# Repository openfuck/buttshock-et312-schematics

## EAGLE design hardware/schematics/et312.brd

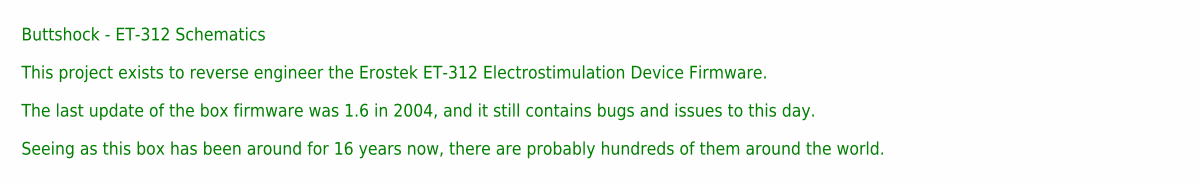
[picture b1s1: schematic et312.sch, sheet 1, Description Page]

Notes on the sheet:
Buttshock - ET-312 Schematics This project exists to reverse engineer the Erostek ET-312 Electrostimulation Device Firmware. The last update of the box firmware was 1.6 in 2004, and it still contains bugs and issues to this day. Seeing as this box has been around for 16 years now, there are probabl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

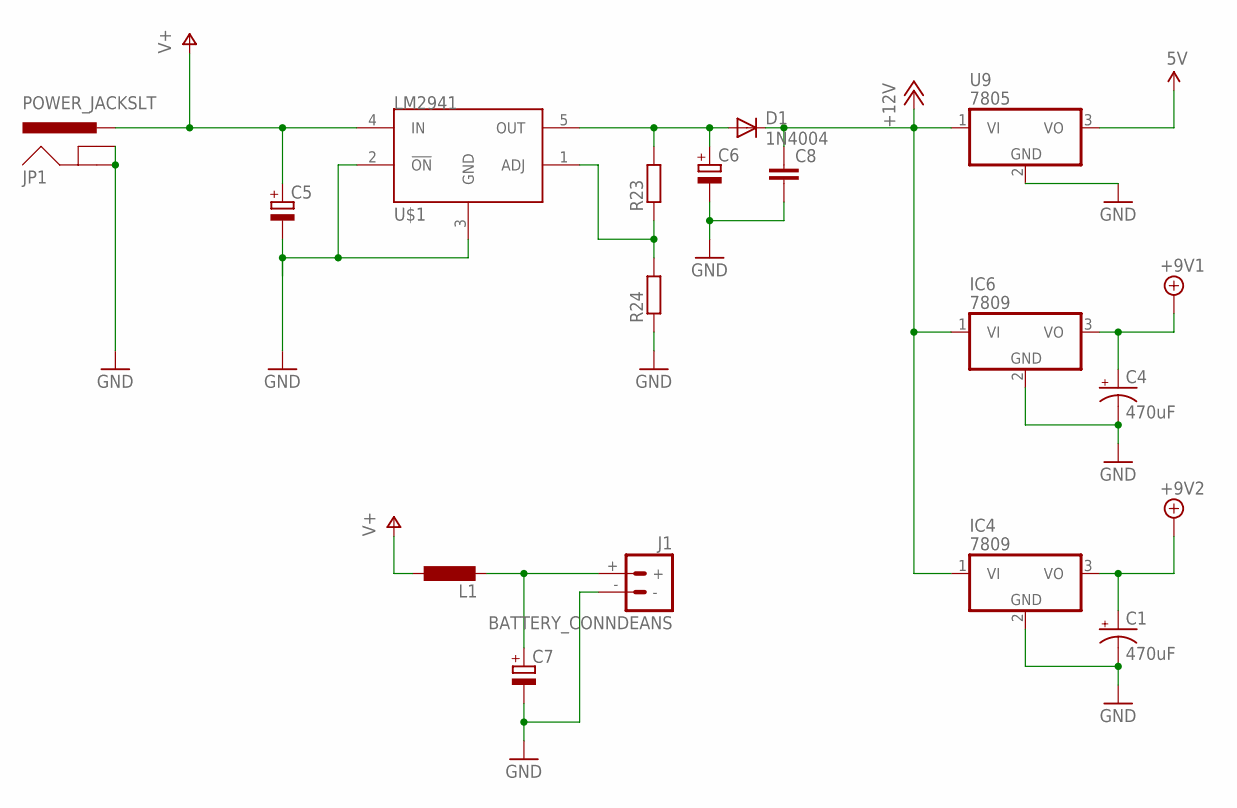
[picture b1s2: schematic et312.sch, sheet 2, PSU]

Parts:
C1, C4: 470uF; CPOL-RADIAL-100UF-25V
C5: CPOL-EUE2.5-6; E2,5-6
C6, C7: CPOL-EUE3.5-10; E3,5-10
C8: C-EU050-025X075; C050-025X075
D1: 1N4004; DO41-10
IC4, IC6: 7809; TO220H
J1: BATTERY_CONNDEANS; DEANS
JP1: POWER_JACKSLT; POWER_JACK_SLOT
L1: L-EU0207/10; 0207/10
R23, R24: R-EU_0204/7; 0204/7
U9: 7805; TO220H
U$1: LM2941; T05A

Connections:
5V: U9.3 (VO); also elsewhere on the board
+9V1: C4.1 (+), IC6.3 (VO); also elsewhere on the board
+9V2: C1.1 (+), IC4.3 (VO); also elsewhere on the board
+12V: C8.1, D1.C, IC4.1 (VI), IC6.1 (VI), U9.1 (VI); also elsewhere on the board
GND: C1.2 (-), C4.2 (-), C5.-, C6.-, C7.-, C8.2, IC4.2 (GND), IC6.2 (GND), J1.-, JP1.GND@1 (GNDBREAK), JP1.GND@2 (GND), R24.1, U9.2 (GND), U$1.2 (!ON), U$1.3 (GND); also elsewhere on the board
unnamed: C7.+, J1.+, L1.2
unnamed: R23.1, R24.2, U$1.1 (ADJ)
unnamed: C6.+, D1.A, R23.2, U$1.5 (OUT)
V+: C5.+, JP1.PWR, L1.1, U$1.4 (IN); also elsewhere on the board

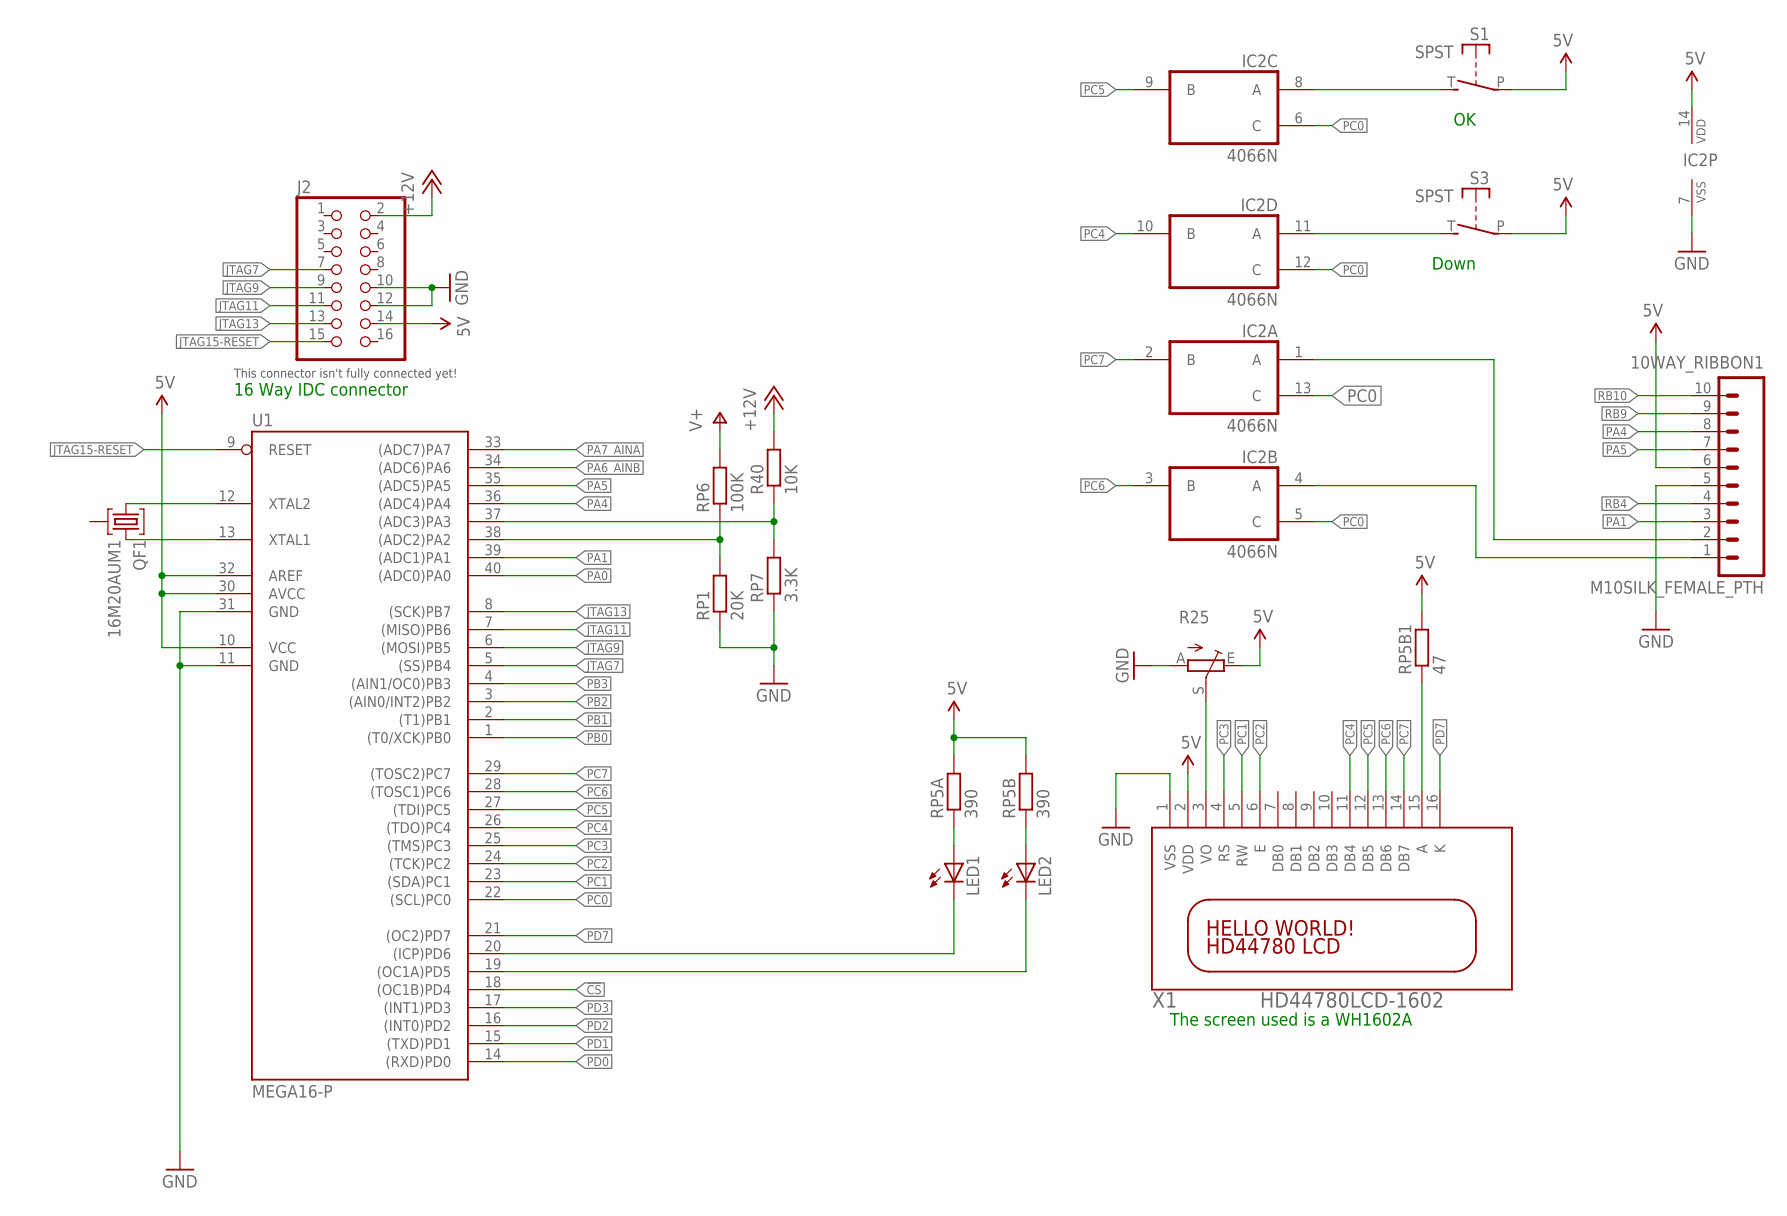
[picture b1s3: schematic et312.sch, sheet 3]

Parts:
10WAY_RIBBON1: M10SILK_FEMALE_PTH; 1X10
IC2: 4066N; DIL14
J2: PINHD-2X8; 2X08
LED1, LED2: LED3MM
QF1: 16M20AUM1; UM1
R25: TRIM_EU-LI10; LI10
R40: 10K; 0207/7
RP1: 20K; 0207/7
RP5A, RP5B: 390; 0207/7
RP5B1: 47; 0207/7
RP6: 100K; 0207/7
RP7: 3.3K; 0207/7
S1, S3: SPST; JUDCOSPST
U1: MEGA16-P; DIL40
X1: HD44780LCD-1602; LCD1602

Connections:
5V: 10WAY_RIBBON1.6, IC2.14 (VDD), J2.14, R25.E, RP5A.2, RP5B.2, RP5B1.2, S1.P, S3.P, U1.10 (VCC), U1.30 (AVCC), U1.32 (AREF), X1.2 (VDD); also elsewhere on the board
!CS: U1.18 ((OC1B)PD4); also elsewhere on the board
+12V: J2.2, R40.2; also elsewhere on the board
GND: 10WAY_RIBBON1.5, IC2.7 (VSS), J2.10, J2.12, R25.A, RP1.1, RP7.1, U1.11 (GND), U1.31 (GND), X1.1 (VSS); also elsewhere on the board
JTAG7: J2.7, U1.5 ((SS)PB4)
JTAG9: J2.9, U1.6 ((MOSI)PB5); also elsewhere on the board
JTAG11: J2.11, U1.7 ((MISO)PB6)
JTAG13: J2.13, U1.8 ((SCK)PB7); also elsewhere on the board
JTAG15-RESET: J2.15, U1.9 (RESET)
unnamed: IC2.8 (A), S1.T (S)
unnamed: IC2.11 (A), S3.T (S)
unnamed: 10WAY_RIBBON1.1, IC2.4 (A)
unnamed: 10WAY_RIBBON1.2, IC2.1 (A)
unnamed: QF1.3, U1.13 (XTAL1)
unnamed: LED2.A, RP5B.1
unnamed: LED1.A, RP5A.1
unnamed: R25.S, X1.3 (VO)
unnamed: QF1.1, U1.12 (XTAL2)
unnamed: RP5B1.1, X1.15 (A)
PA0: U1.40 ((ADC0)PA0); also elsewhere on the board
PA1: 10WAY_RIBBON1.3, U1.39 ((ADC1)PA1); also elsewhere on the board
PA4: 10WAY_RIBBON1.8, R40.1, RP7.2, U1.36 ((ADC4)PA4), U1.37 ((ADC3)PA3)
PA5: 10WAY_RIBBON1.7, RP1.2, RP6.1, U1.35 ((ADC5)PA5), U1.38 ((ADC2)PA2)
PA6_AINB: U1.34 ((ADC6)PA6); also elsewhere on the board
PA7_AINA: U1.33 ((ADC7)PA7); also elsewhere on the board
PB0: U1.1 ((T0/XCK)PB0); also elsewhere on the board
PB1: U1.2 ((T1)PB1); also elsewhere on the board
PB2: U1.3 ((AIN0/INT2)PB2); also elsewhere on the board
PB3: U1.4 ((AIN1/OC0)PB3); also elsewhere on the board
PC0: IC2.5 (C), IC2.6 (C), IC2.12 (C), IC2.13 (C), U1.22 ((SCL)PC0)
PC1: U1.23 ((SDA)PC1), X1.5 (RW)
PC2: U1.24 ((TCK)PC2), X1.6 (E)
PC3: U1.25 ((TMS)PC3), X1.4 (RS)
PC4: IC2.10 (B), U1.26 ((TDO)PC4), X1.11 (DB4)
PC5: IC2.9 (B), U1.27 ((TDI)PC5), X1.12 (DB5)
PC6: IC2.3 (B), U1.28 ((TOSC1)PC6), X1.13 (DB6)
PC7: IC2.2 (B), U1.29 ((TOSC2)PC7), X1.14 (DB7)
PD0: U1.14 ((RXD)PD0); also elsewhere on the board
PD1: U1.15 ((TXD)PD1); also elsewhere on the board
PD2: U1.16 ((INT0)PD2); also elsewhere on the board
PD3: U1.17 ((INT1)PD3); also elsewhere on the board
PD5: LED2.K (C), U1.19 ((OC1A)PD5)
PD6: LED1.K (C), U1.20 ((ICP)PD6)
PD7: U1.21 ((OC2)PD7), X1.16 (K)
RB4: 10WAY_RIBBON1.4; also elsewhere on the board
RB9: 10WAY_RIBBON1.9; also elsewhere on the board
RB10: 10WAY_RIBBON1.10; also elsewhere on the board
V+: RP6.2; also elsewhere on the board

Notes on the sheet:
16 Way IDC connector
The screen used is a WH1602A
Down
This connector isn't fully connected yet!

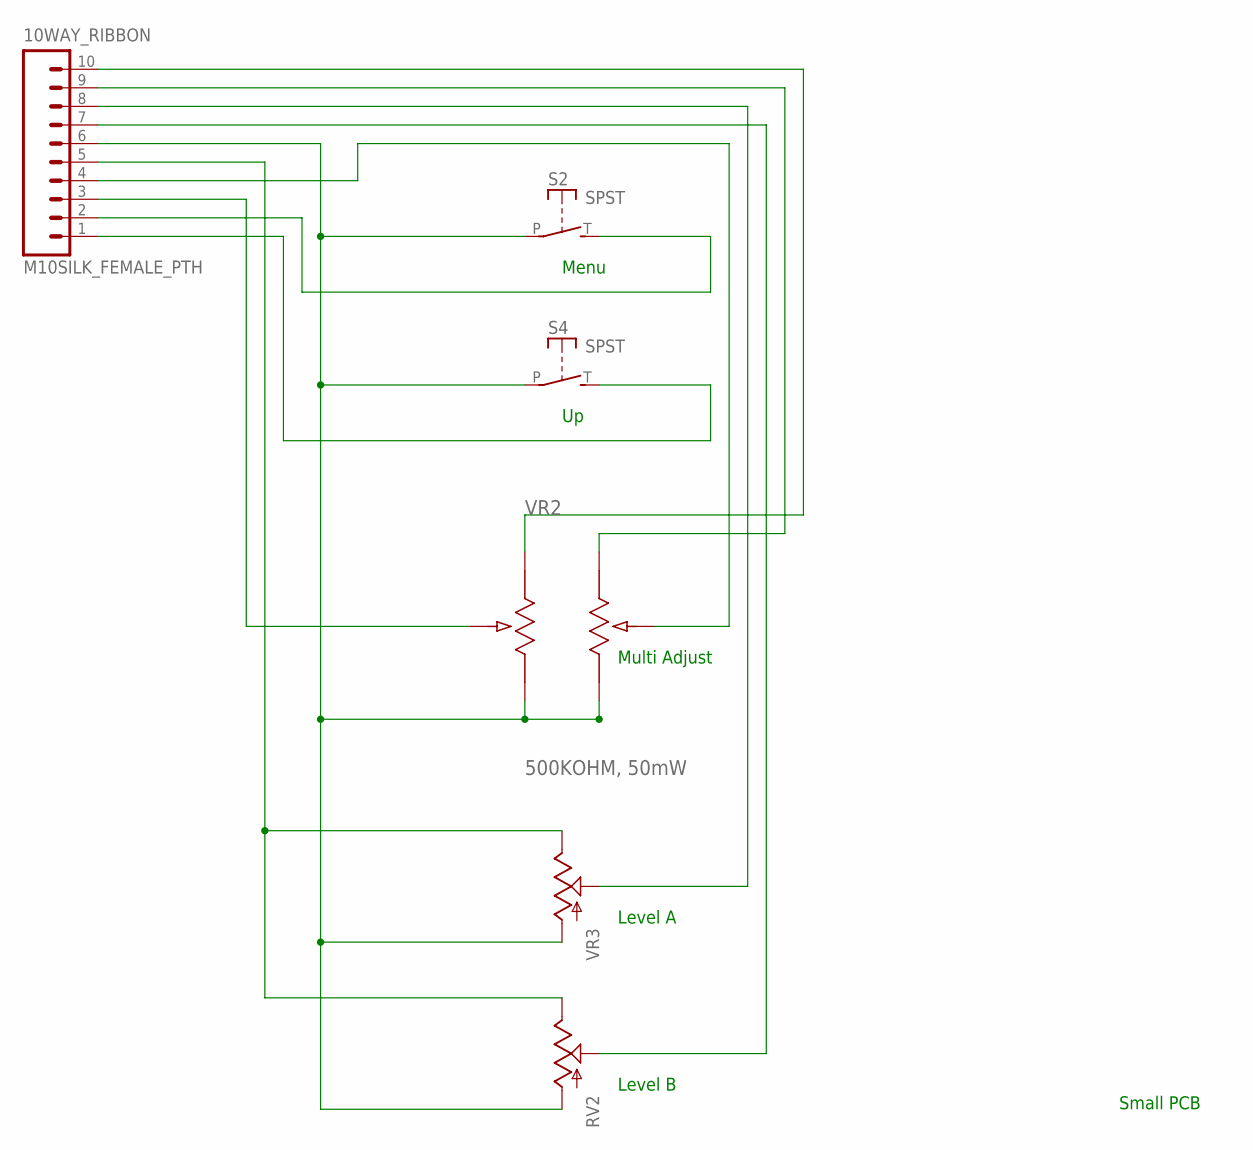
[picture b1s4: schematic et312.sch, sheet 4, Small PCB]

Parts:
10WAY_RIBBON: M10SILK_FEMALE_PTH; 1X10
RV2: POT; ALPS_POT
S2, S4: SPST; JUDCOSPST
VR2: 500KOHM, 50mW; POT_EVJC20
VR3: POT; ALPS_POT

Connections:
unnamed: 10WAY_RIBBON.6, RV2.P$3 (A), S2.P, S4.P, VR2.1, VR2.1', VR3.P$3 (A)
unnamed: 10WAY_RIBBON.2, S2.T (S)
unnamed: 10WAY_RIBBON.1, S4.T (S)
unnamed: 10WAY_RIBBON.9, VR2.3'
unnamed: 10WAY_RIBBON.8, VR3.P$2 (S)
unnamed: 10WAY_RIBBON.7, RV2.P$2 (S)
unnamed: 10WAY_RIBBON.10, VR2.3
unnamed: 10WAY_RIBBON.4, VR2.2'
unnamed: 10WAY_RIBBON.3, VR2.2
VR4: 10WAY_RIBBON.5, RV2.P$1 (E), VR3.P$1 (E)

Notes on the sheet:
Small PCB
Menu
Level A
Level B
Multi Adjust

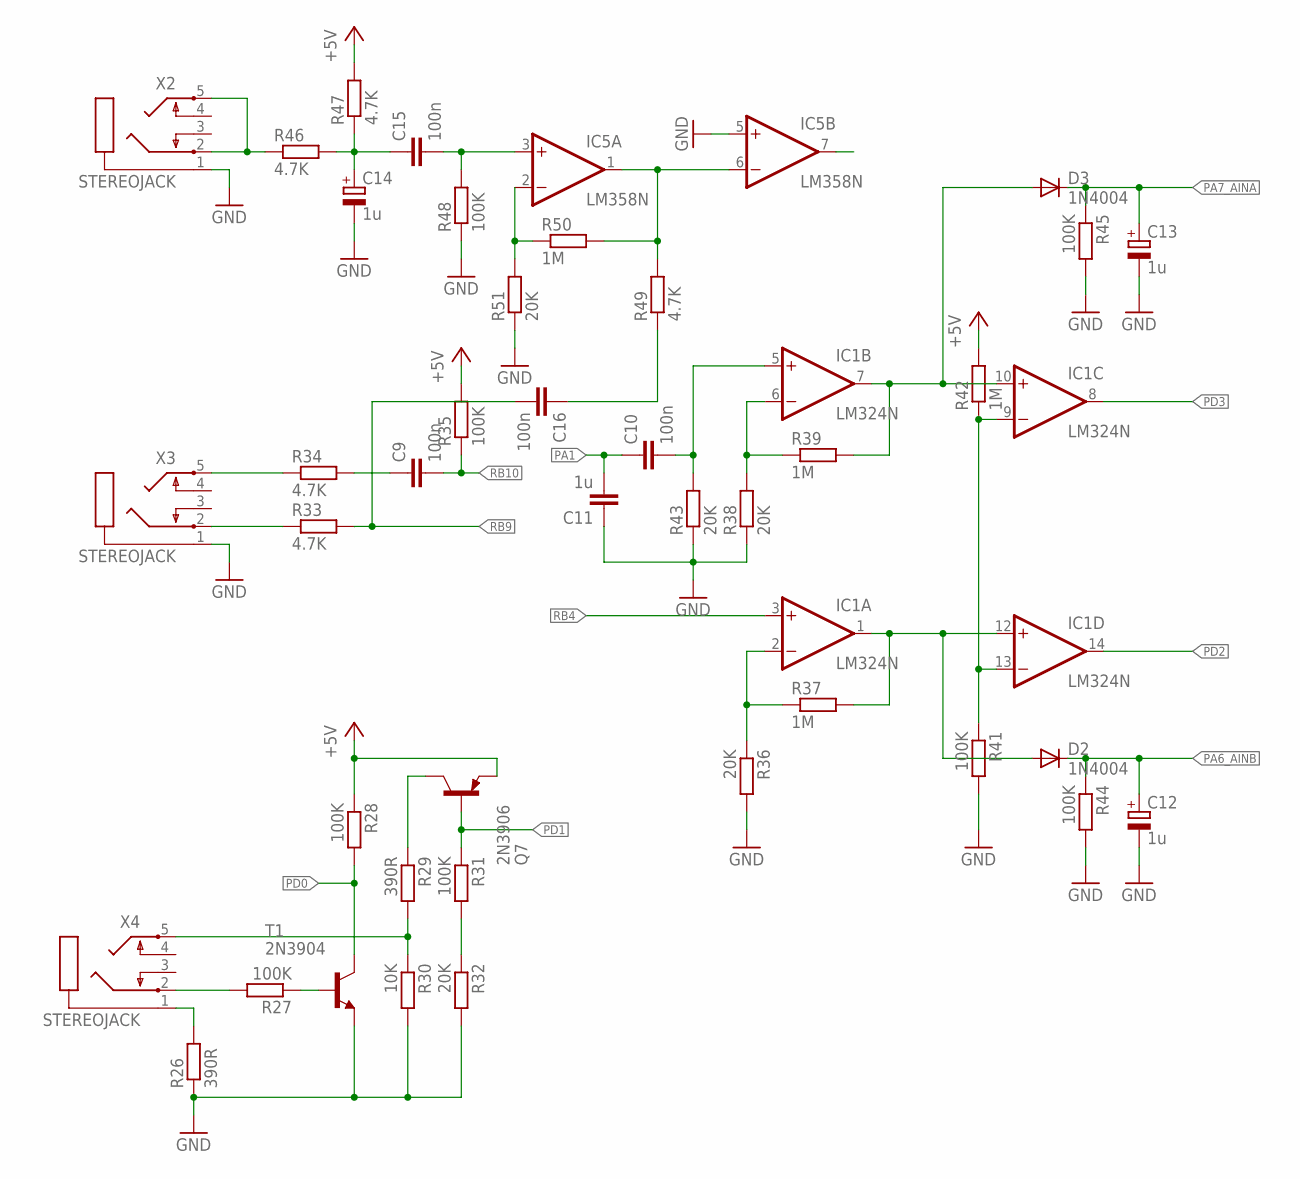
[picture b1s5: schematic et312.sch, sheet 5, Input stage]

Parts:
C9, C10, C15, C16: 100n; C050-025X075
C11: 1u; C050-025X075
C12, C13, C14: 1u; E2,5-5
D2, D3: 1N4004; DO41-10
IC1: LM324N; DIL14
IC5: LM358N; DIL08
Q7: 2N3906; TO92
R26, R29: 390R; 0207/10
R27, R28, R31, R35, R41, R44, R45, R48: 100K; 0207/10
R30: 10K; 0207/10
R32, R36, R38, R43, R51: 20K; 0207/10
R33, R34, R46, R47, R49: 4.7K; 0207/10
R37, R39, R42, R50: 1M; 0207/10
T1: 2N3904; TO92
X2, X3, X4: STEREOJACK; STX3100

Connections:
+5V: Q7.3 (E), R28.1, R35.2, R42.2, R47.2
GND: C11.1, C12.-, C13.-, C14.-, IC5.5 (+IN), R26.1, R30.2, R32.2, R36.2, R38.1, R41.2, R43.1, R44.2, R45.2, R48.1, R51.1, T1.3 (E), X2.1, X3.1; also elsewhere on the board
unnamed: R26.2, X4.1
unnamed: R29.2, R30.1, X4.5
unnamed: R27.2, X4.2
unnamed: R27.1, T1.2 (B)
unnamed: R31.2, R32.1
unnamed: Q7.1 (C), R29.1
unnamed: IC1.2 (-IN), R36.1, R37.1
unnamed: D2.A, IC1.1 (OUT), IC1.12 (+IN), R37.2
unnamed: R33.1, X3.2
unnamed: R34.1, X3.5
unnamed: C9.1, R34.2
unnamed: IC1.6 (-IN), R38.2, R39.1
unnamed: IC1.9 (-IN), IC1.13 (-IN), R41.1, R42.1
unnamed: C10.2, IC1.5 (+IN), R43.2
unnamed: D3.A, IC1.7 (OUT), IC1.10 (+IN), R39.2
unnamed: R46.1, X2.2, X2.5
unnamed: C14.+, C15.1, R46.2, R47.1
unnamed: C15.2, IC5.3 (+IN), R48.2
unnamed: IC5.2 (-IN), R50.1, R51.2
unnamed: IC5.1 (OUT), IC5.6 (-IN), R49.2, R50.2
unnamed: C16.1, R49.1
PA1: C10.1, C11.2; also elsewhere on the board
PA6_AINB: C12.+, D2.C, R44.1; also elsewhere on the board
PA7_AINA: C13.+, D3.C, R45.1; also elsewhere on the board
PD0: R28.2, T1.1 (C); also elsewhere on the board
PD1: Q7.2 (B), R31.1; also elsewhere on the board
PD2: IC1.14 (OUT); also elsewhere on the board
PD3: IC1.8 (OUT); also elsewhere on the board
RB4: IC1.3 (+IN); also elsewhere on the board
RB9: C16.2, R33.2; also elsewhere on the board
RB10: C9.2, R35.1; also elsewhere on the board
V+: IC1.4 (V+), IC5.8 (V+); also elsewhere on the board
V-: IC1.11 (V-), IC5.4 (V-)

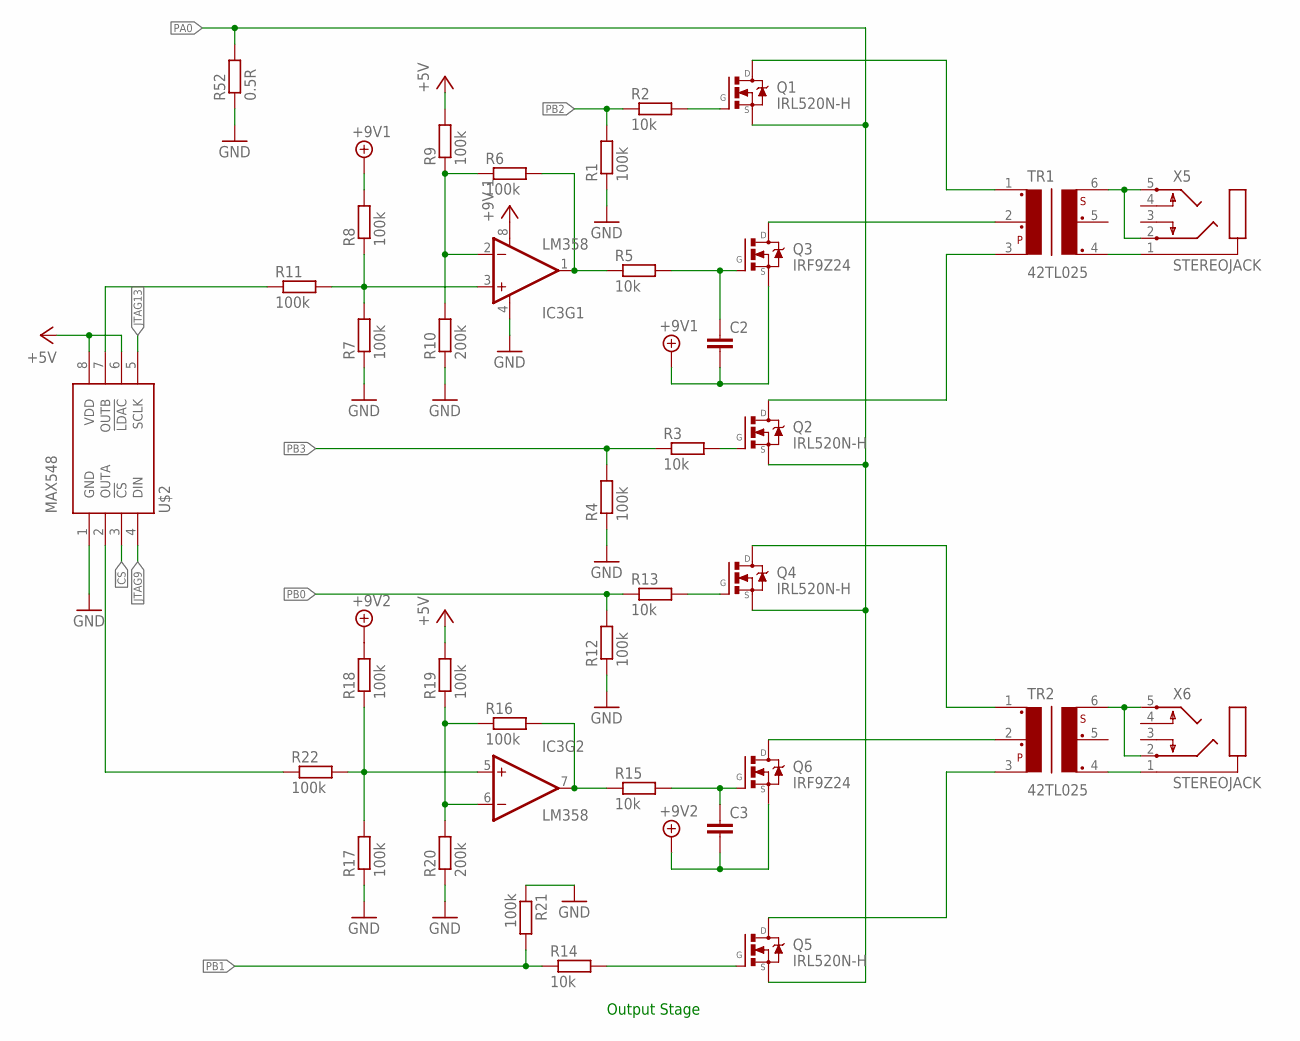
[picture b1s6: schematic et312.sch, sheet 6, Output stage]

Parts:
C2, C3: CAPPTH; CAP-PTH-SMALL
IC3: LM358; DIP08
Q1, Q2, Q4, Q5: IRL520N-H; TO220
Q3, Q6: IRF9Z24; TO220
R1, R4, R6, R7, R8, R9, R11, R12, R16, R17, R18, R19, R21, R22: 100k; 0207/10
R2, R3, R5, R13, R14, R15: 10k; 0207/10
R10, R20: 200k; 0207/10
R52: 0.5R; 0207/10
TR1, TR2: 42TL025; 42TL
U$2: MAX548; DIL08
X5, X6: STEREOJACK; STX3100

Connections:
!CS: U$2.3 (!CS); also elsewhere on the board
+9V1: C2.2, Q3.3 (S), R8.2; also elsewhere on the board
+9V2: C3.2, Q6.3 (S), R18.2; also elsewhere on the board
GND: IC3.4 (V-), R1.1, R4.1, R7.1, R10.1, R12.1, R17.1, R20.1, R21.1, R52.1, U$2.1 (GND); also elsewhere on the board
JTAG9: U$2.4 (DIN); also elsewhere on the board
JTAG13: U$2.5 (SCLK); also elsewhere on the board
unnamed: TR1.4, X5.1
unnamed: TR1.6, X5.2, X5.5
unnamed: Q1.1 (G), R2.2
unnamed: Q2.1 (G), R3.2
unnamed: IC3.1 (OUT), R5.1, R6.2
unnamed: C2.1, Q3.1 (G), R5.2
unnamed: IC3.3 (+IN), R7.2, R8.1, R11.2
unnamed: Q4.1 (G), R13.2
unnamed: Q5.1 (G), R14.2
unnamed: IC3.7 (OUT), R15.1, R16.2
unnamed: C3.1, Q6.1 (G), R15.2
unnamed: IC3.5 (+IN), R17.2, R18.1, R22.2
unnamed: R22.1, U$2.2 (OUTA)
unnamed: Q1.2 (D), TR1.1
unnamed: Q3.2 (D), TR1.2
unnamed: Q4.2 (D), TR2.1
unnamed: Q6.2 (D), TR2.2
unnamed: Q5.2 (D), TR2.3
unnamed: Q2.2 (D), TR1.3
unnamed: IC3.2 (-IN), R6.1, R9.1, R10.2
unnamed: IC3.6 (-IN), R16.1, R19.1, R20.2
unnamed: R11.1, U$2.7 (OUTB)
unnamed: TR2.6, X6.2, X6.5
unnamed: TR2.4, X6.1
PA0: Q1.3 (S), Q2.3 (S), Q4.3 (S), Q5.3 (S), R52.2; also elsewhere on the board
PB0: R12.2, R13.1; also elsewhere on the board
PB1: R14.1, R21.2; also elsewhere on the board
PB2: R1.2, R2.1; also elsewhere on the board
PB3: R3.1, R4.2; also elsewhere on the board
VCC: IC3.8 (V+), R9.2, R19.2, U$2.6 (!LDAC), U$2.8 (VDD)

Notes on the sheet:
Output Stage

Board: 2 copper layers, 119 parts (0 on the bottom side), 111 nets, no tracks yet.

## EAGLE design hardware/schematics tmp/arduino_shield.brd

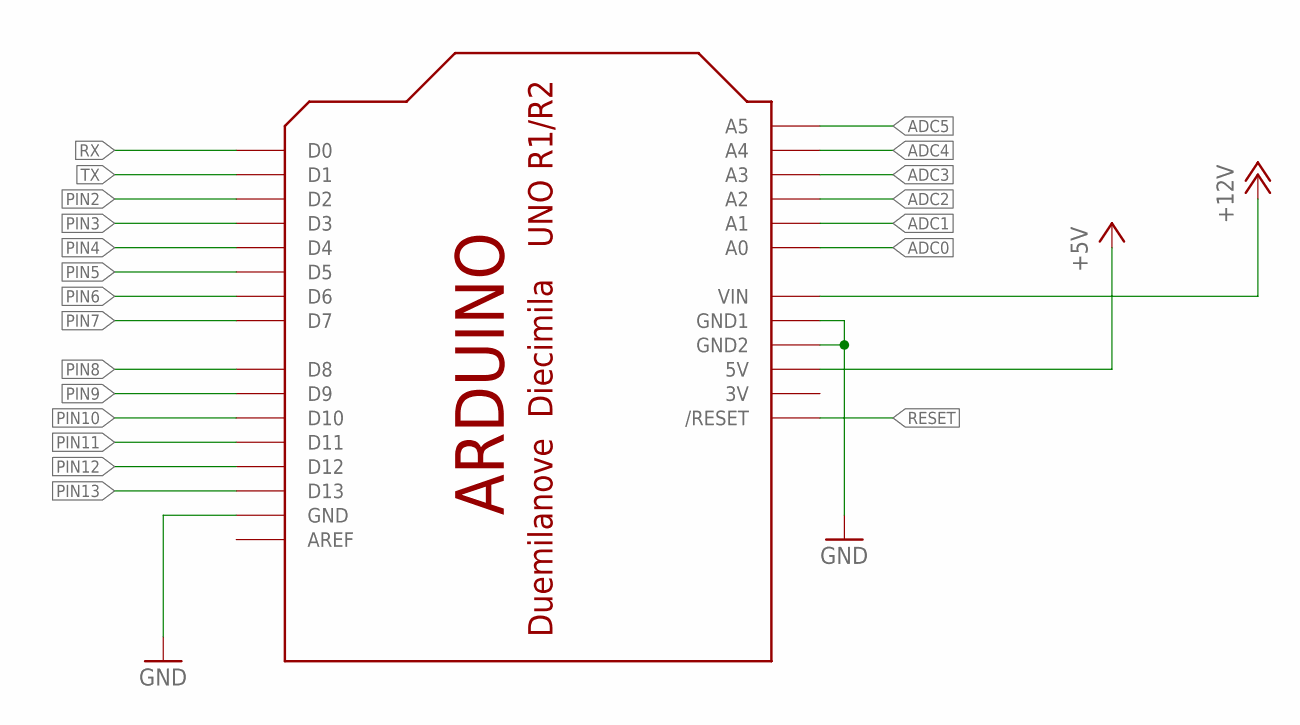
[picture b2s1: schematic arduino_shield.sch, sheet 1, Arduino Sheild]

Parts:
GND: ARDUINOUNO; ARDUINO

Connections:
3V: GND.3V
+5V: GND.5V; also elsewhere on the board
+12V: GND.VIN; also elsewhere on the board
ADC0: GND.A0
ADC1: GND.A1; also elsewhere on the board
ADC2: GND.A2
ADC3: GND.A3
ADC4: GND.A4
ADC5: GND.A5
GND: GND.GND, GND.GND1, GND.GND2; also elsewhere on the board
PIN2: GND.D2
PIN3: GND.D3; also elsewhere on the board
PIN4: GND.D4; also elsewhere on the board
PIN5: GND.D5; also elsewhere on the board
PIN6: GND.D6; also elsewhere on the board
PIN7: GND.D7
PIN8: GND.D8
PIN9: GND.D9; also elsewhere on the board
PIN10: GND.D10
PIN11: GND.D11; also elsewhere on the board
PIN12: GND.D12
PIN13: GND.D13; also elsewhere on the board
RESET: GND.RESET (/RESET)
RX: GND.D0
TX: GND.D1

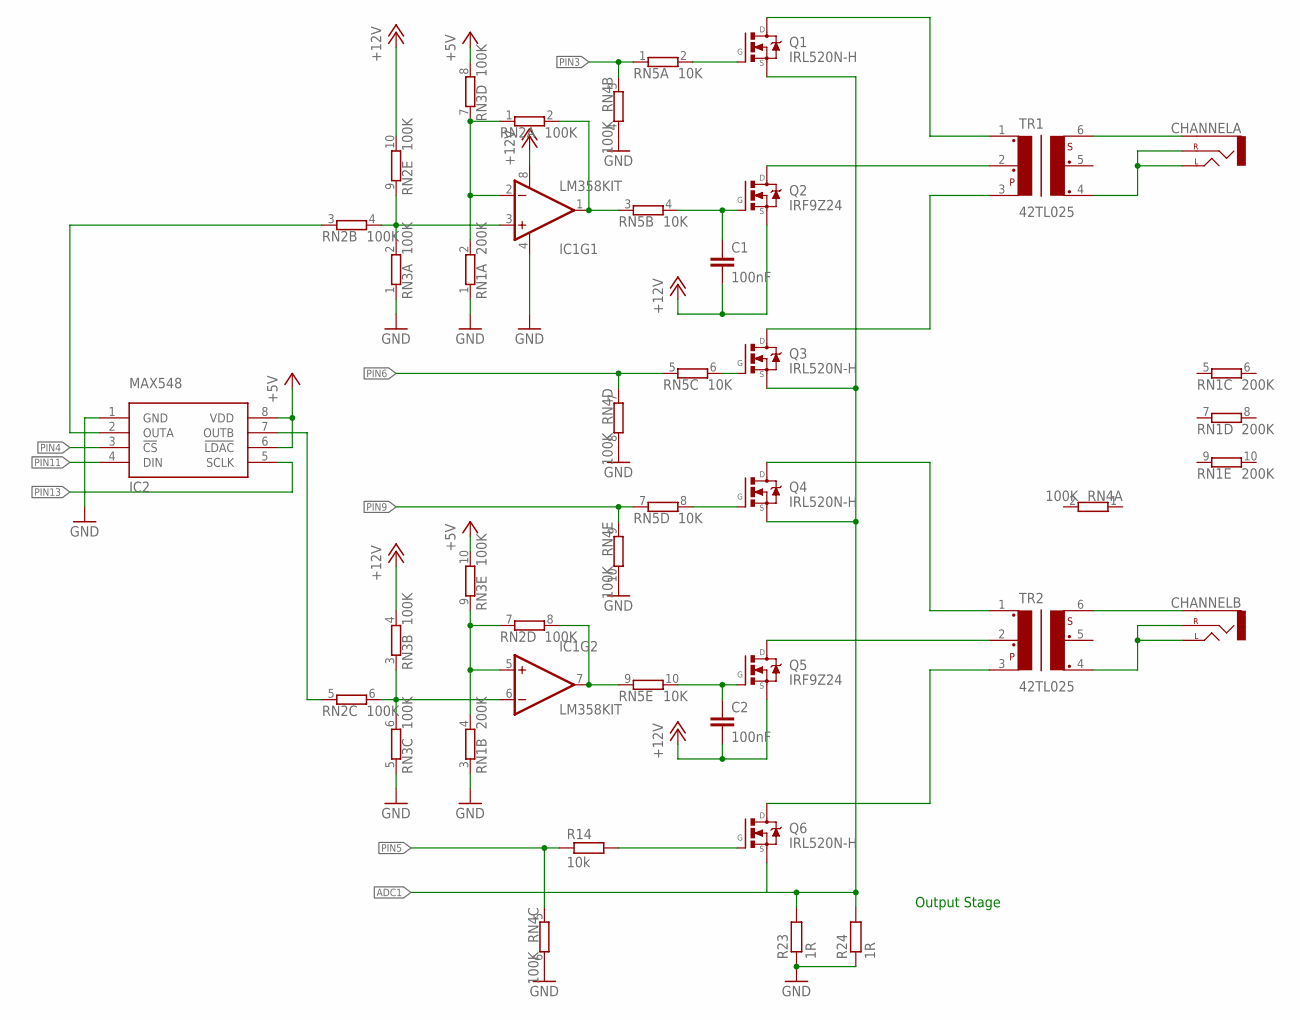
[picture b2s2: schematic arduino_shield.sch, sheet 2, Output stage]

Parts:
C1, C2: 100nF; C2.5-2
CHANNELA: AUDIO-JACK2.5MM; STEREOJACK2.5MM_STEREOJACK2.5MM
CHANNELB: AUDIO-JACK2.5MM; STEREOJACK2.5MM_STEREOJACK2.5MM
IC1: LM358KIT; DIP08-KIT
IC2: MAX548; DIL08
Q1, Q3, Q4, Q6: IRL520N-H; TO220V
Q2, Q5: IRF9Z24; TO220V
R14: 10k; R0805
R23, R24: 1R; R0805
RN1: 200K; SIL10
RN2, RN3, RN4: 100K; SIL10
RN5: 10K; SIL10
TR1, TR2: 42TL025; 42TL

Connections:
+5V: IC2.6 (!LDAC), IC2.8 (VDD), RN3.8 (2), RN3.10 (2); also elsewhere on the board
+12V: C1.2, C2.2, IC1.8 (V+), Q2.3 (S), Q5.3 (S), RN2.10 (2), RN3.4 (2); also elsewhere on the board
ADC1: Q1.3 (S), Q3.3 (S), Q4.3 (S), Q6.3 (S), R23.2, R24.2; also elsewhere on the board
GND: IC1.4 (V-), IC2.1 (GND), R23.1, R24.1, RN1.1, RN1.3 (1), RN3.1, RN3.5 (1), RN4.4 (2), RN4.6 (2), RN4.8 (2), RN4.10 (2); also elsewhere on the board
unnamed: CHANNELA.RING1 (SLEEVE), TR1.6
unnamed: CHANNELB.RING1 (SLEEVE), TR2.6
unnamed: CHANNELB.SHIELD (LEFT), CHANNELB.TIP (RIGHT), TR2.4
unnamed: CHANNELA.SHIELD (LEFT), CHANNELA.TIP (RIGHT), TR1.4
unnamed: IC2.2 (OUTA), RN2.3 (1)
unnamed: IC2.7 (OUTB), RN2.5 (1)
unnamed: Q1.1 (G), RN5.2
unnamed: Q3.1 (G), RN5.6 (2)
unnamed: IC1.1 (OUT), RN2.2, RN5.3 (1)
unnamed: C1.1, Q2.1 (G), RN5.4 (2)
unnamed: IC1.3 (+IN), RN2.4 (2), RN2.9 (1), RN3.2
unnamed: Q4.1 (G), RN5.8 (2)
unnamed: Q6.1 (G), R14.2
unnamed: IC1.7 (OUT), RN2.8 (2), RN5.9 (1)
unnamed: C2.1, Q5.1 (G), RN5.10 (2)
unnamed: IC1.6 (-IN), RN2.6 (2), RN3.3 (1), RN3.6 (2)
unnamed: Q1.2 (D), TR1.1
unnamed: Q2.2 (D), TR1.2
unnamed: Q4.2 (D), TR2.1
unnamed: Q5.2 (D), TR2.2
unnamed: Q6.2 (D), TR2.3
unnamed: Q3.2 (D), TR1.3
unnamed: IC1.2 (-IN), RN1.2, RN2.1, RN3.7 (1)
unnamed: IC1.5 (+IN), RN1.4 (2), RN2.7 (1), RN3.9 (1)
PIN3: RN4.3 (1), RN5.1; also elsewhere on the board
PIN4: IC2.3 (!CS); also elsewhere on the board
PIN5: R14.1, RN4.5 (1); also elsewhere on the board
PIN6: RN4.7 (1), RN5.5 (1); also elsewhere on the board
PIN9: RN4.9 (1), RN5.7 (1); also elsewhere on the board
PIN11: IC2.4 (DIN); also elsewhere on the board
PIN13: IC2.5 (SCLK); also elsewhere on the board

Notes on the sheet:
Output Stage

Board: 2 copper layers, 23 parts (0 on the bottom side), 35 nets, no tracks yet.

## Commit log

2016-04-26 Git Ignore
    Try and keep my mac and eagle files away from teh repository
2016-04-26 Added blank schematic
2016-04-27 PCB WIP
    Layed down uC and some other componants
2016-04-27 Added small board
    Added 2 buttons, and two pots to the small board, found the CD4066 in dip, and added to new sheet.
2016-04-27 CDB4066 added
    Control pins are listed as connected to pin 22 on uC, 22 is listed as a ground… can some one please check!
2016-04-27 fixed uC
    picked up a atmega16 rather than atmega8
2016-04-28 Added PDF
    work done on schematic, PDF generated for people who don't have eagle.
2016-04-28 Schematic update
    Added screen, finished buttons
2016-04-29 https://xkcd.com/1296/
2016-04-29 added folder for hardware description
2016-04-29 moved folder to hardware
2016-04-29 further work on the schematics
2016-04-30 Updated Schematics
    WIP
2016-04-30 moved datasheets
2016-04-30 PCB WIP
    Added more to the PCB
2016-04-30 update name on Pg1
    Sheet one updated
2016-05-01 Added more component datasheets
2016-05-01 Deleted Project file
    Project files are redundent, and there is not advantage to having one (also stores path and licence information in this).
2016-05-01 Snapshot of Eagle files as PDF
    Snapshot of Eagle files as PDF
    because these are binary blobs, will snapshot spairingly.
2016-05-02 Addded datasheet
2016-05-02 Added datasheet
2016-05-09 Added (hopefully) complete schematics of my Rev.E Unit. Most of the work was done by @hurgotron. Only old school hand drawn for now :)
2016-05-10 Add images submodule
2016-05-10 Ignore firmware directory
2016-05-10 updated with output stage
    brought in Flocked's output stage, WIP
2016-05-10 Added missing RP1(3) on the second opamp of U2
2016-05-10 Added missing RP4(4) and RP4(5) on Q7 and Q8 inputs
2016-05-10 Remove wrong representation of RP3. It's actually the same as RP4
2016-05-10 Schematics
    Name Nets
2016-05-10 Schematics
    Continues Clean up
2016-05-10 Schematics PDF update
    this is a snapshot of the schematics as of 2016/05/10 23:12 Skippy's Local Time
2016-05-10 Schematics PDF update
    This is a snapshot of the schematics as of 2016/05/10 23:12 Skippy's Local Time -- something stupid with pdf
2016-05-10 Schematics
    WIP
2016-05-11 schemtaics
    wip
2016-05-12 Schematics
    more wip
2016-05-21 Updates to schematics, based on hand drawn schematics
2016-05-25 Datasheet
    Added datasheet for Transformer
2016-05-25 Remove old schematics
    Remove old schematics that have had no work on them for a while.
2016-05-25 Starting an Arduino Sheild
2016-05-25 Work on Schematics
2016-05-25 Better Transfromer
2016-06-01 Arduino Sheild Eagle
2016-06-17 Testing to see if resistor networks help
2016-06-19 nope mcnopeface
2016-06-19 Changes by FluffyBit
    done:
    - changed grid to 0.1mm to help place components
    - forced all components onto 0.1mm grid
    - added gnd plane on bottom of board
    - added two caps for decoupling the DAC+OP-AMP
    - added 10K pull-up on the nCS line to the DAC
2016-06-19 Pin Swap
    et312.sch page 6 vs 03_output_stage_1.gif, bottom opamp (pins 5 & 6)
2016-06-28 cleanup and new pdfs

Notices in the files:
parts and their libraries:
SparkFun-AnalogIC: Licensing:Creative Commons ShareAlike 4.0 International - https://creativecommons.org/licenses/by-sa/4.0
